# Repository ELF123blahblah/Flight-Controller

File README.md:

# Flight-Controller
Flight controller for a drone

This flight controller was specifically made to be compatible with Mission planner

This is one of my finest creation. All my previous versions were on breadboard.

### Reason for its creation

I created this flight controller to have a try and fulfill my childhood dream of trying out a FPV drone. I have always felt that it was one of the coolest things and wanted to try it out since i was 10.

### How to use 

This model is a part of a larger drone model I will make in the future and it will be powered using BEC protocol from the ESC of the motors of the drone.

### BOM
- LMR51430
- Magnetometer ---> LIS3MDLTR
- Microcontroller ---> STM32H743VIT6_C114409
- Barometer ---> BMP580
- USB-C ---> TYPE-C 16PIN 2MD(073)
- IMU ---> ICM-45686
- GPS --->  MAX-M10S 
- Antenna ---> SMA-KWE902
- Battery charger ---> BQ25756RRVR

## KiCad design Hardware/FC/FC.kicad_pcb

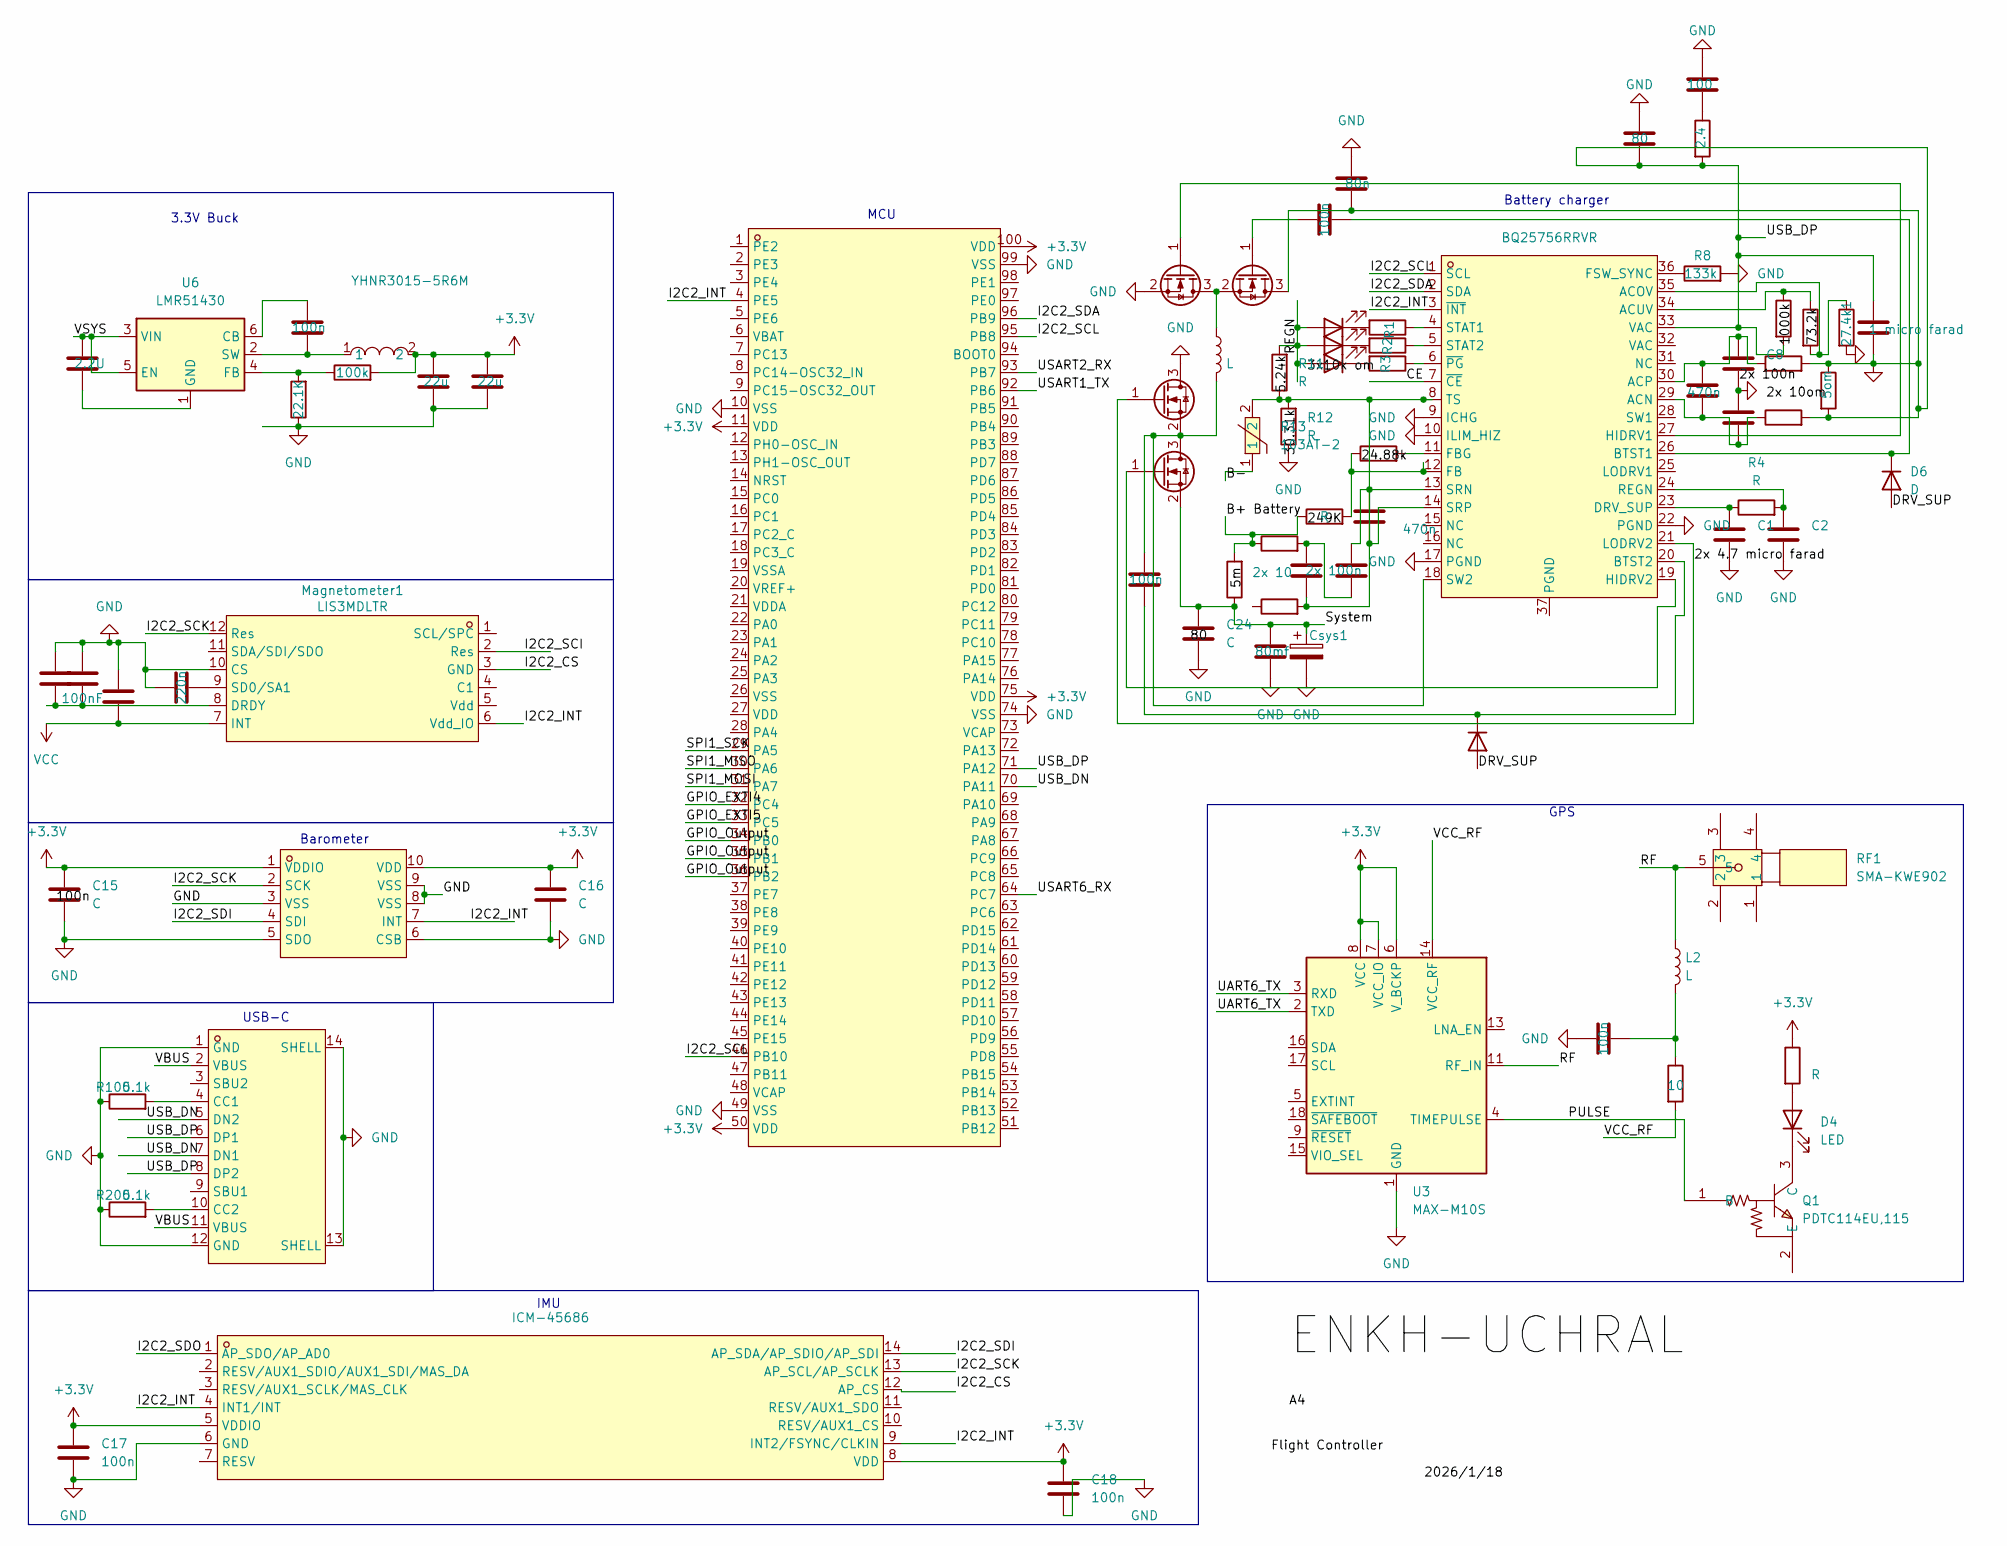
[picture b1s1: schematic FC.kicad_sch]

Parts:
2.4: R; R_0402_1005Metric
27.4k1: 1 micro farad; C_0402_1005Metric
C1, C2, C8, C11, C15, C16, C20, C21, C24: C; C_0402_1005Metric
C3: 100; C_0402_1005Metric
C4, C5, C9: 470n; C_0402_1005Metric
C6: 2x 100n; C_0402_1005Metric
C7: 80mf; C_0402_1005Metric
C10: 2.2U; C_0402_1005Metric
C12, C17, C18, C23, C25, C26: 100n; C_0402_1005Metric
C13, C14: 22u; C_0402_1005Metric
C19: 220n; C_0402_1005Metric
C22: 100nF; C_0402_1005Metric
C27: 80n; C_0402_1005Metric
C28: 80; C_0402_1005Metric
Csys1: C_Polarized; C_0402_1005Metric
D1, D2, D3, D4: LED; LED_0402_1005Metric
D5: 1N4148WT; D_SOD-523
D6: D; LED_0402_1005Metric
L1: YHNR3015-5R6M; IND-SMD_L3.0-W3.0; LCSC Part C18236327
L2, L3: L; IND-SMD_L3.0-W3.0
Magnetometer1: LIS3MDLTR; LGA-16_L3.0-W3.0-P0.50-BL; LCSC Part C478483
Q1: PDTC114EU,115; SOT-323-3_L2.0-W1.3-P1.30-LS2.1-BR; LCSC Part C135830
Q2, Q3, Q4, Q5: Q_NMOS_GSD; SOT-323-3_L2.0-W1.3-P1.30-LS2.1-BR
R1, R2, R3, R4, R9, R10, R11, R12, R14, R16, R17, R18, R22: R; R_0201_0603Metric
R5: 1000k om; R_0201_0603Metric
R6, R7: 27.4k om; R_0201_0603Metric
R8: 133k; R_0201_0603Metric
R13: 103AT-2; R_0201_0603Metric; LCSC Part C5346323
R15: 2x 10; R_0201_0603Metric
R19: 5om; R_0201_0603Metric
R20: 100k; R_0201_0603Metric
R21: 22.1K; R_0201_0603Metric
R23: 10; R_0201_0603Metric
R100, R200: 5.1k; R_0201_0603Metric
RF1: SMA-KWE902; SMA-TH_SMA-KWE902; LCSC Part C914554
U1: STM32H743VIT6_C114409; LQFP-100_L14.0-W14.0-P0.50-LS16.0-BL; LCSC Part C114409
U2: ICM-45686; LGA-14_L3.0-W2.5-P0.50-TL; LCSC Part C22459454
U3: MAX-M10S; ublox_MAX
U4: BMP580; LGA-10_L2.0-W2.0-P0.50-TL_BMP580; LCSC Part C22391138
U5: BQ25756RRVR; TQFN-36_L6.0-W5.0-P0.50-BL-EP-1; LCSC Part C19272232
U6: LMR51430; SOT-23-6
USB1: TYPE-C 16PIN 2MD(073); USB-C-SMD_TYPE-C-6PIN-2MD-073; LCSC Part C2765186

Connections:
73.2k om: 2.4.2, 27.4k1.1, 27.4k1.2, C27.1, C28.2, Q5.3 (D), R5.2, R17.2, R18.2, R19.1, R19.2, U1.71 (PA12), U5.33 (VAC), USB1.6 (DP1), USB1.8 (DP2)
+3.3V: C13.1, C14.1, C15.1, C16.1, C17.1, C18.2, L1.2, R20.2, R22.1, U1.11 (VDD), U1.50 (VDD), U1.75 (VDD), U1.100 (VDD), U2.5 (VDDIO), U2.8 (VDD), U3.6 (V_BCKP), U3.7 (VCC_IO), U3.8 (VCC), U4.1 (VDDIO), U4.10 (VDD)
/2x 4.7 micro farad: Q3.1 (G), U5.21 (LODRV2)
/73.2k: R6.2, R7.1, U5.35 (ACOV)
/B+: R10.1, R14.1, R16.2
/B-: R13.1
/CE: U5.7 (~CE)
/DRV_SUP: D5.2 (A), D6.2 (A)
/GPIO_EXTI4: U1.32 (PC4)
/GPIO_EXTI5: U1.33 (PC5)
/GPIO_Output: U1.34 (PB0), U1.35 (PB1), U1.36 (PB2)
/I2C2_CS: Magnetometer1.3 (GND)
/I2C2_INT: Magnetometer1.6 (Vdd_IO), U1.4 (PE5), U2.4 (INT1/INT), U2.9 (INT2/FSYNC/CLKIN), U4.7 (INT), U5.3 (~INT)
/I2C2_SCI: Magnetometer1.2 (Res)
/I2C2_SCK: Magnetometer1.12 (Res), U2.13 (AP_SCL/AP_SCLK), U4.2 (SCK)
/I2C2_SCL: U1.46 (PB10), U1.95 (PB8), U5.1 (SCL)
/I2C2_SDA: U1.96 (PB9), U5.2 (SDA)
/I2C2_SDI: U2.14 (AP_SDA/AP_SDIO/AP_SDI), U4.4 (SDI)
/I2C2_SDO: U2.1 (AP_SDO/AP_AD0)
/PULSE: Q1.1 (B), U3.4 (TIMEPULSE)
/REGN: D1.2 (A), D2.2 (A), D3.2 (A), R11.2
/RF: L2.1, RF1.5, U3.11 (RF_IN)
/SPI1_MISO: U1.30 (PA6)
/SPI1_MOSI: U1.31 (PA7)
/SPI1_SCK: U1.29 (PA5)
/System: C7.1, C24.1, Csys1.1, Q2.2 (S), R16.1
/UART6_TX: U3.2 (TXD), U3.3 (RXD)
/USART1_TX: U1.92 (PB6)
/USART2_RX: U1.93 (PB7)
/USART6_RX: U1.64 (PC7)
/USB_DN: U1.70 (PA11), USB1.5 (DN2), USB1.7 (DN1)
/VBUS: USB1.2 (VBUS), USB1.11 (VBUS)
/VCC_RF: R23.2, U3.14 (VCC_RF)
/VSYS: C10.1, U6.3 (VIN), U6.5 (EN)
GND: C1.2, C2.2, C3.1, C7.2, C8.2, C11.1, C13.2, C14.2, C15.2, C16.2, C17.2, C18.1, C19.1, C20.1, C21.1, C22.1, C23.1, C24.2, C27.2, C28.1, Csys1.2, Magnetometer1.10 (CS), Q3.3 (D), Q4.2 (S), R7.2, R8.2, R12.1, R21.1, R100.1, R200.1, U1.10 (VSS), U1.49 (VSS), U1.74 (VSS), U1.99 (VSS), U2.6 (GND), U3.1 (GND), U3.10 (GND), U3.12 (GND), U4.3 (VSS), U4.5 (SDO), U4.6 (CSB), U4.8 (VSS), U4.9 (VSS), U5.9 (ICHG), U5.10 (ILIM_HIZ), U5.17 (PGND), U5.22 (PGND), USB1.1 (GND), USB1.12 (GND), USB1.13 (SHELL), USB1.14 (SHELL)
unnamed: 2.4.1, C3.2
unnamed: C5.2, C6.1, R14.2
unnamed: C23.2, L2.2, R23.1
unnamed: D1.1 (K), R3.2
unnamed: D2.1 (K), R2.2
unnamed: D3.1 (K), R1.2
unnamed: D4.2 (A), R22.2
unnamed: D4.1 (K), Q1.3 (C)
unnamed: C25.2, D5.1 (K), U5.20 (BTST2)
unnamed: C26.2, D6.1 (K), U5.26 (BTST1)
unnamed: C21.2, C22.2, Magnetometer1.8 (DRDY)
unnamed: C19.2, Magnetometer1.9 (SD0/SA1)
unnamed: C25.1, L3.2, Q2.3 (D), Q3.2 (S), U5.18 (SW2)
unnamed: Q2.1 (G), U5.19 (HIDRV2)
unnamed: L3.1, Q4.3 (D), Q5.2 (S)
unnamed: Q4.1 (G), U5.27 (HIDRV1)
unnamed: C26.1, Q5.1 (G)
unnamed: C9.2, C11.2, R17.1, U5.29 (ACN)
unnamed: C8.1, C9.1, R18.1, U5.30 (ACP)
unnamed: R5.1, R6.1, U5.34 (ACUV)
unnamed: C1.1, R4.1, U5.23 (DRV_SUP)
unnamed: R9.1, R10.2, U5.12 (FB)
unnamed: R9.2, U5.11 (FBG)
unnamed: R8.1, U5.36 (FSW_SYNC)
unnamed: C2.1, R4.2, U5.24 (REGN)
unnamed: C4.1, C4.2, C5.1, C6.2, R11.1, R12.2, R13.2, R15.2, U5.8 (TS), U5.13 (SRN), U5.14 (SRP)
unnamed: R1.1, U5.4 (STAT1)
unnamed: R2.1, U5.5 (STAT2)
unnamed: R3.1, U5.6 (~PG)
unnamed: C12.1, U6.6 (CB)
unnamed: R20.1, R21.2, U6.4 (FB)
unnamed: C10.2, U6.1 (GND)
unnamed: C12.2, L1.1, U6.2 (SW)
unnamed: R100.2, USB1.4 (CC1)
unnamed: R200.2, USB1.10 (CC2)
VCC: C20.2, Magnetometer1.7 (INT)

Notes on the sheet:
Barometer
IMU
Battery charger
MCU
3.3V Buck
USB-C
GPS

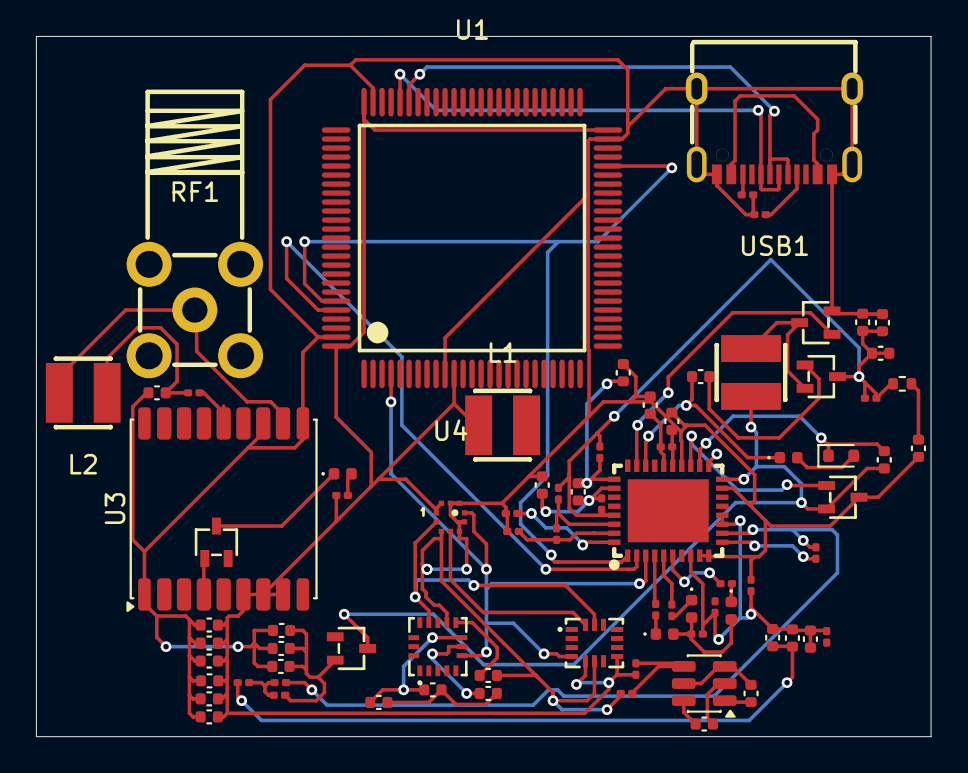
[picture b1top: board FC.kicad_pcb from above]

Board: 2 copper layers, 49.7 x 38.9 mm, 79 parts (0 on the bottom side), 58 nets.

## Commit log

2026-02-23 Clean up README.md formatting
    Removed extra blank lines and improved formatting.
2026-02-24 Inputing all the files
2026-03-20 hopefully final commit
